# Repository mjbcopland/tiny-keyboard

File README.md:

# Tiny Keyboard

Design files and example code for my ATtiny85 1-key keyboard.

&nbsp;

## Related links

* **[V-USB](https://www.obdev.at/products/vusb/index.html)**  
  Software USB communication for AVR

* **[Micronucleus](https://github.com/micronucleus/micronucleus)**  
  Bootloader and tools used to program the keyboard

* **[DigistumpArduino](https://github.com/digistump/DigistumpArduino)**  
  ATtiny85 support for the Arduino IDE

* **[r/MechanicalKeyboards](https://www.reddit.com/r/MechanicalKeyboards/)**  
  For more keyboard science

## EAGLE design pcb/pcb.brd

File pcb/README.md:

<https://oshpark.com/shared_projects/BiJILe6J>

 ![PCB Bottom](
  https://644db4de3505c40a0444-327723bce298e3ff5813fb42baeefbaa.ssl.cf1.rackcdn.com/e19cd20724890d95d69d246827d4af95.png
)

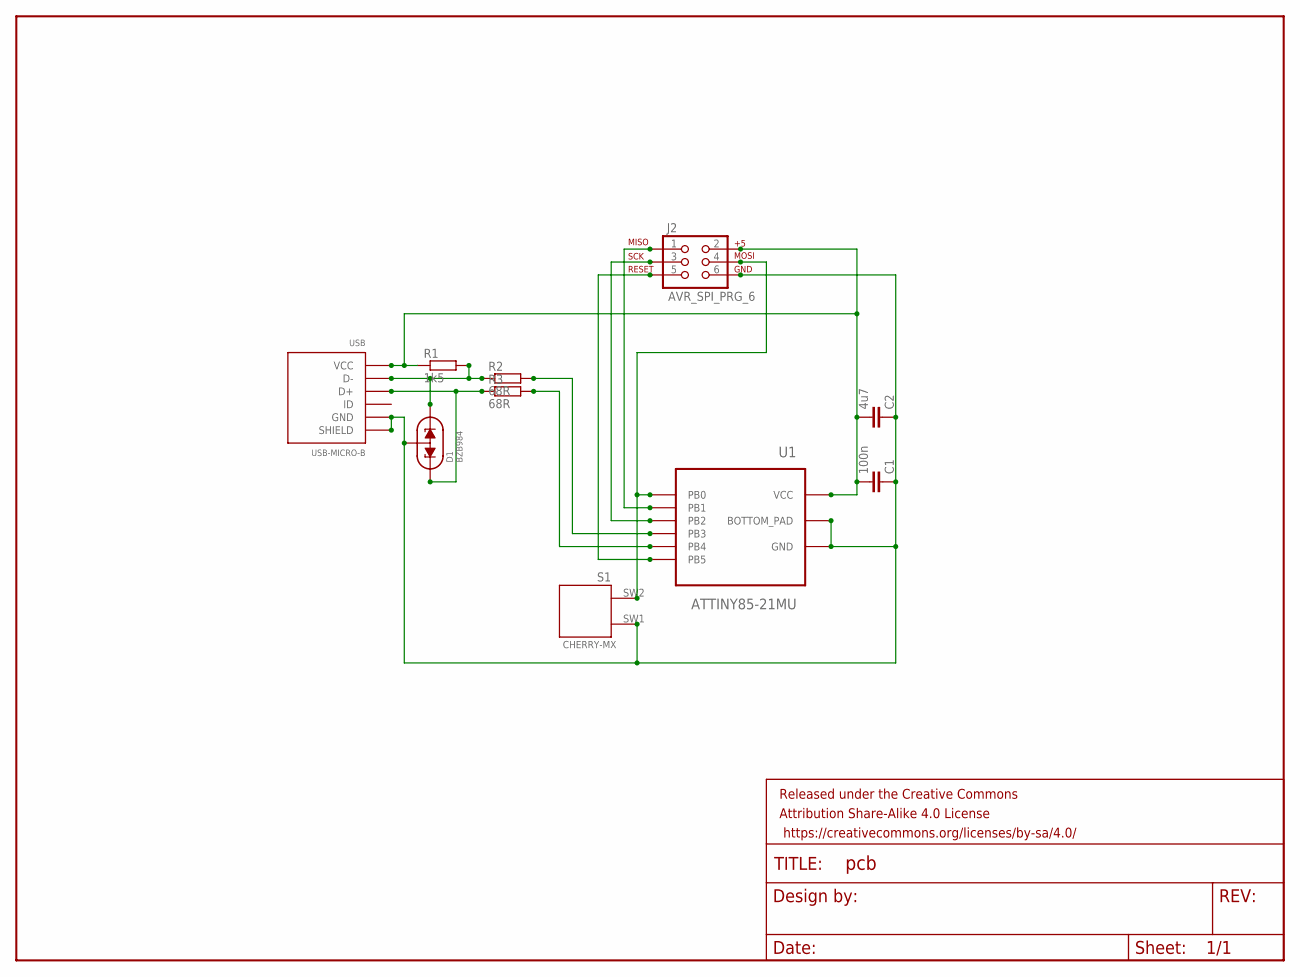
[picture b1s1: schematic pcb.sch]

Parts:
C1: 100n; C0603
C2: 4u7; C0603
D1: BZB984; SOT663
FRAME1: FRAME-LETTERNO_PACKAGE; DUMMY
J2: AVR_SPI_PRG_6; 2X3_PADS
R1: 1k5; R0603
R2, R3: 68R; R0603
S1: CHERRY-MX-PLATE
U1: ATTINY85-21MU; QFN-20-4MM
USB: USB-MICRO-B; MICRO-USB-B

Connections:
D+: R3.2, U1.5 (PB4)
D-: R2.2, U1.2 (PB3)
GND: C1.1, C2.1, D1.3 (ANODE), J2.6, S1.SW1 (PIN-1), U1.8 (GND), U1.21 (BOTTOM_PAD), USB.5 (GND), USB.P$1 (SHIELD), USB.P$2 (SHIELD), USB.P$3 (SHIELD), USB.P$4 (SHIELD), USB.SHIELD1 (SHIELD), USB.SHIELD2 (SHIELD), USB.SHIELD3 (SHIELD), USB.SHIELD3A (SHIELD), USB.SHIELD4 (SHIELD), USB.SHIELD5 (SHIELD), USB.SHIELD6 (SHIELD), USB.SHIELD6A (SHIELD)
unnamed: J2.1, U1.12 (PB1)
unnamed: J2.4, S1.SW2 (PIN-2), U1.11 (PB0)
unnamed: J2.3, U1.14 (PB2)
unnamed: D1.2 (CATHODE2), R1.2, R2.1, USB.2 (D-)
unnamed: D1.1 (CATHODE1), R3.1, USB.3 (D+)
unnamed: C1.2, C2.2, J2.2, R1.1, U1.15 (VCC), USB.1 (VCC)
unnamed: J2.5, U1.1 (PB5)

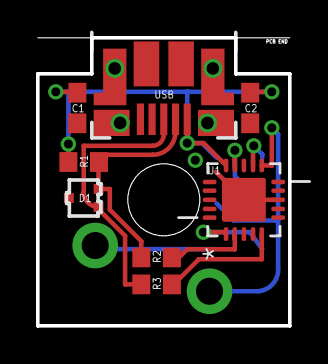
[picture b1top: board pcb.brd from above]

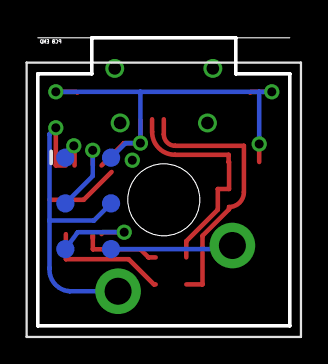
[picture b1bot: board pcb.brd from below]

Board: 2 copper layers, 14.0 x 16.0 mm, 11 parts (2 on the bottom side), 10 nets.

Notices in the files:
parts and their libraries:
SparkFun-Aesthetics: Licensing: Creative Commons ShareAlike 4.0 International - https://creativecommons.org/licenses/by-sa/4.0
SparkFun-Aesthetics: Released under the Creative Commons Attribution Share-Alike 4.0 License
SparkFun-Aesthetics: https://creativecommons.org/licenses/by-sa/4.0
